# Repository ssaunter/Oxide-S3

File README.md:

# Oxide-S3
Oxide-S3 is a retro Spotify interface featuring a large TFT screen, a small OLED screen, 6 tactile switches, and 2 rotary encoders, all running on an ESP32-WROOM-1.

The device uses three seperate PCBs, one for the front, one for the top, and one for the side. The front PCB includes the displays, LiPo battery management, the MCU, and USB-C for charging. The top PCB includes the 6 Cherry MX Blue switches, and one of the rotary encoders. The side PCB simply includes the final rotary encoder. The small PCBs are connected to the front PCB using JST-XH cables.

# The PCBs

Front PCB:

Top PCB:

Side PCB:

Schematic:

# Assembly

The assembly is performed in several steps. First, 8 M3x5x5 threaded inserts are installed to the standoffs in the 3D printed front case. Then, the three PCBs are secured using M3x6 bolts.

 After the PCBs are installed, the battery holder module is press-fit into the front case, and the LiPo battery (red) is slid into place.

Then, the speaker and back case are press-fit into place. There is a 0.2mm tolerance built into the CAD model. 

Finally, the side and top knob are  press-fit onto the rotary encoders. This concludes the assembly.

# Software

Taking inspiration from [Donatnan Jong](https://github.com/Dongathan-Jong), I plan to utilize Spotify's built-in [developer interface](https://developer.spotify.com/) and Adafruit display libraries to program the screens in the Arduino IDE. Since Wifi is easily handled by the ESP32 and the switches handled by Spotify's interface, the main focus would be on managing the displays. Given my short project turnaround time, I will update this repo once parts arrive.

The TFT screen will be controlled through SPI, and the OLED through I2C. To add images, I'll use a bitmap tool to add features. Below are the major functions of the two displays:

Required Libraries:
---
```
#include <Arduino.h>
#include <ArduinoJson.h>
#include <Adafruit_GFX.h>
#include <Adafruit_ST7735.h>
#include <WiFi.h>
#include <SpotifyEsp32.h>
#include <SPI.h>
```

|3.5" TFT|
| :---: |
|Spotify symbol|
|Song timestamp|
|Audio wave animation|
|Key switch/encoder map|
|Album navigation|
|Spotify username|

|0.91" OLED|
| :---: |
|Battery charge status|
|Clock|
|Volume/Mute symbol|
|Wifi status|

Like I mentioned, this project is super last minute (started less than a day ago). I'll write the code and update this repo once I recieve the parts, and show off what the Oxide-S3 can do. Here's an example of how simple the code can be, written by [Donatnan Jong](https://github.com/Dongathan-Jong/SpotifyDisplay/?tab=readme-ov-file):

# BOM

| Part | Quantity | Price Per | Link | 
| :--- | :---: | :---: | :--- |
| **0.91" OLED** | 1 | $1.95 | [AliExpress](https://www.aliexpress.us/item/3256806449757543.html) |
| **3.5" TFT** | 1 | $10.45 | [AliExpress](https://www.aliexpress.us/item/3256801812264108.html) |  
| **ESP32-S3-WROOM-1-N8R8** | 1 | $6.13 | [DigiKey](https://www.digikey.com/short/wq4p3rwv) |
| **LDO** | 1 | $0.22 | [DigiKey](https://www.digikey.com/short/b2m9hq2c) |
| **Battery Charger** | 1 | $0.47 | [DigiKey](https://www.digikey.com/short/dz9hbfw5) |
| **USB-C Recepticle** | 1 | $0.78 | [DigiKey](https://www.digikey.com/short/rnhfh9zp) |
| **Rotary Encoder** | 2 | $1.72 | [DigiKey](https://www.digikey.com/short/1mq4zdpt) |
| **Boot Button** | 1 | $0.56 |[DigiKey](https://www.digikey.com/short/q5bt28qt) |
| **Slide Switch** | 1 | $0.65 | [DigiKey](https://www.digikey.com/short/41mc094h) |
| **1x2 JST-PH** | 1 | $0.11 | [DigiKey](https://www.digikey.com/short/41b2w40z) |
| **1x10 JST-XH** | 2 | $0.32 |[DigiKey](https://www.digikey.com/short/5571c5z5) |
| **1x4 JST-XH** | 2 | $0.14 | [DigiKey](https://www.digikey.com/short/h5trn14w) |
| **1.2k R 0603** | 1 | $0.10 |[DigiKey](https://www.digikey.com/short/hnr0jfrp) |
| **5.1k R 0603** | 2 | $0.10 |[DigiKey](https://www.digikey.com/short/mmd3843z) |
| **10k R 0603** | 1 | $0.10 | [DigiKey](https://www.digikey.com/short/p59dnbn3) |
| **0.1uF C 0603** | 2 | $0.12 |[DigiKey](https://www.digikey.com.au/short/w83wjqbv) |
| **10uF C 0603** | 2 | $0.35 |[DigiKey](https://www.digikey.com/short/5dtppp4z) |
| **DSA Keycaps 10pcs** | 1 | (have) |[DigiKey](https://www.digikey.com/short/p4j0ztf5) |
| **Cherry MX Blue 10pcs** | 1 | $4.00 |[MechanicalKeyboards](https://mechanicalkeyboards.com/products/cherry-mx-blue-60g-clicky) |
| **1x10 JST-XH Jumper** | 1 | $3.40 |[AliExpress](https://www.aliexpress.us/item/3256807069159656.html) |
| **1x4 JST-XH Jumper** | 1 | $2.36 |[AliExpress](https://www.aliexpress.us/item/3256807069159656.html) |
| **1S 1500mAh LiPo** | 1 | (have) |[SparkFun](https://www.sparkfun.com/lithium-ion-battery-1500mah-iec62133-certified.html#content-documentation) |
| **MicroSD** | 1 | (have) | |
| **M3x6 Bolt** | 8 | (have) | |
| **M3x5x5 Threaded Insert** | 8 | (have) | |

Totals
---
| Service  | Price | 
| :--- | :--- |
| **JLCPCB Order** | $48.49 | |
| **DigiKey Order** | $32.36 | 
| **AliExpress Order** |  $19.44 | 
| **MechanicalKeyboards Order** |  $9.52 | 

This total comes out to $109.81 which is slightly over my limit. I'll downgrade to some generic Cherry MX Red switches, and some old DSA switches, both which I alreday have bringing the total to **$94.34**.

Orders:

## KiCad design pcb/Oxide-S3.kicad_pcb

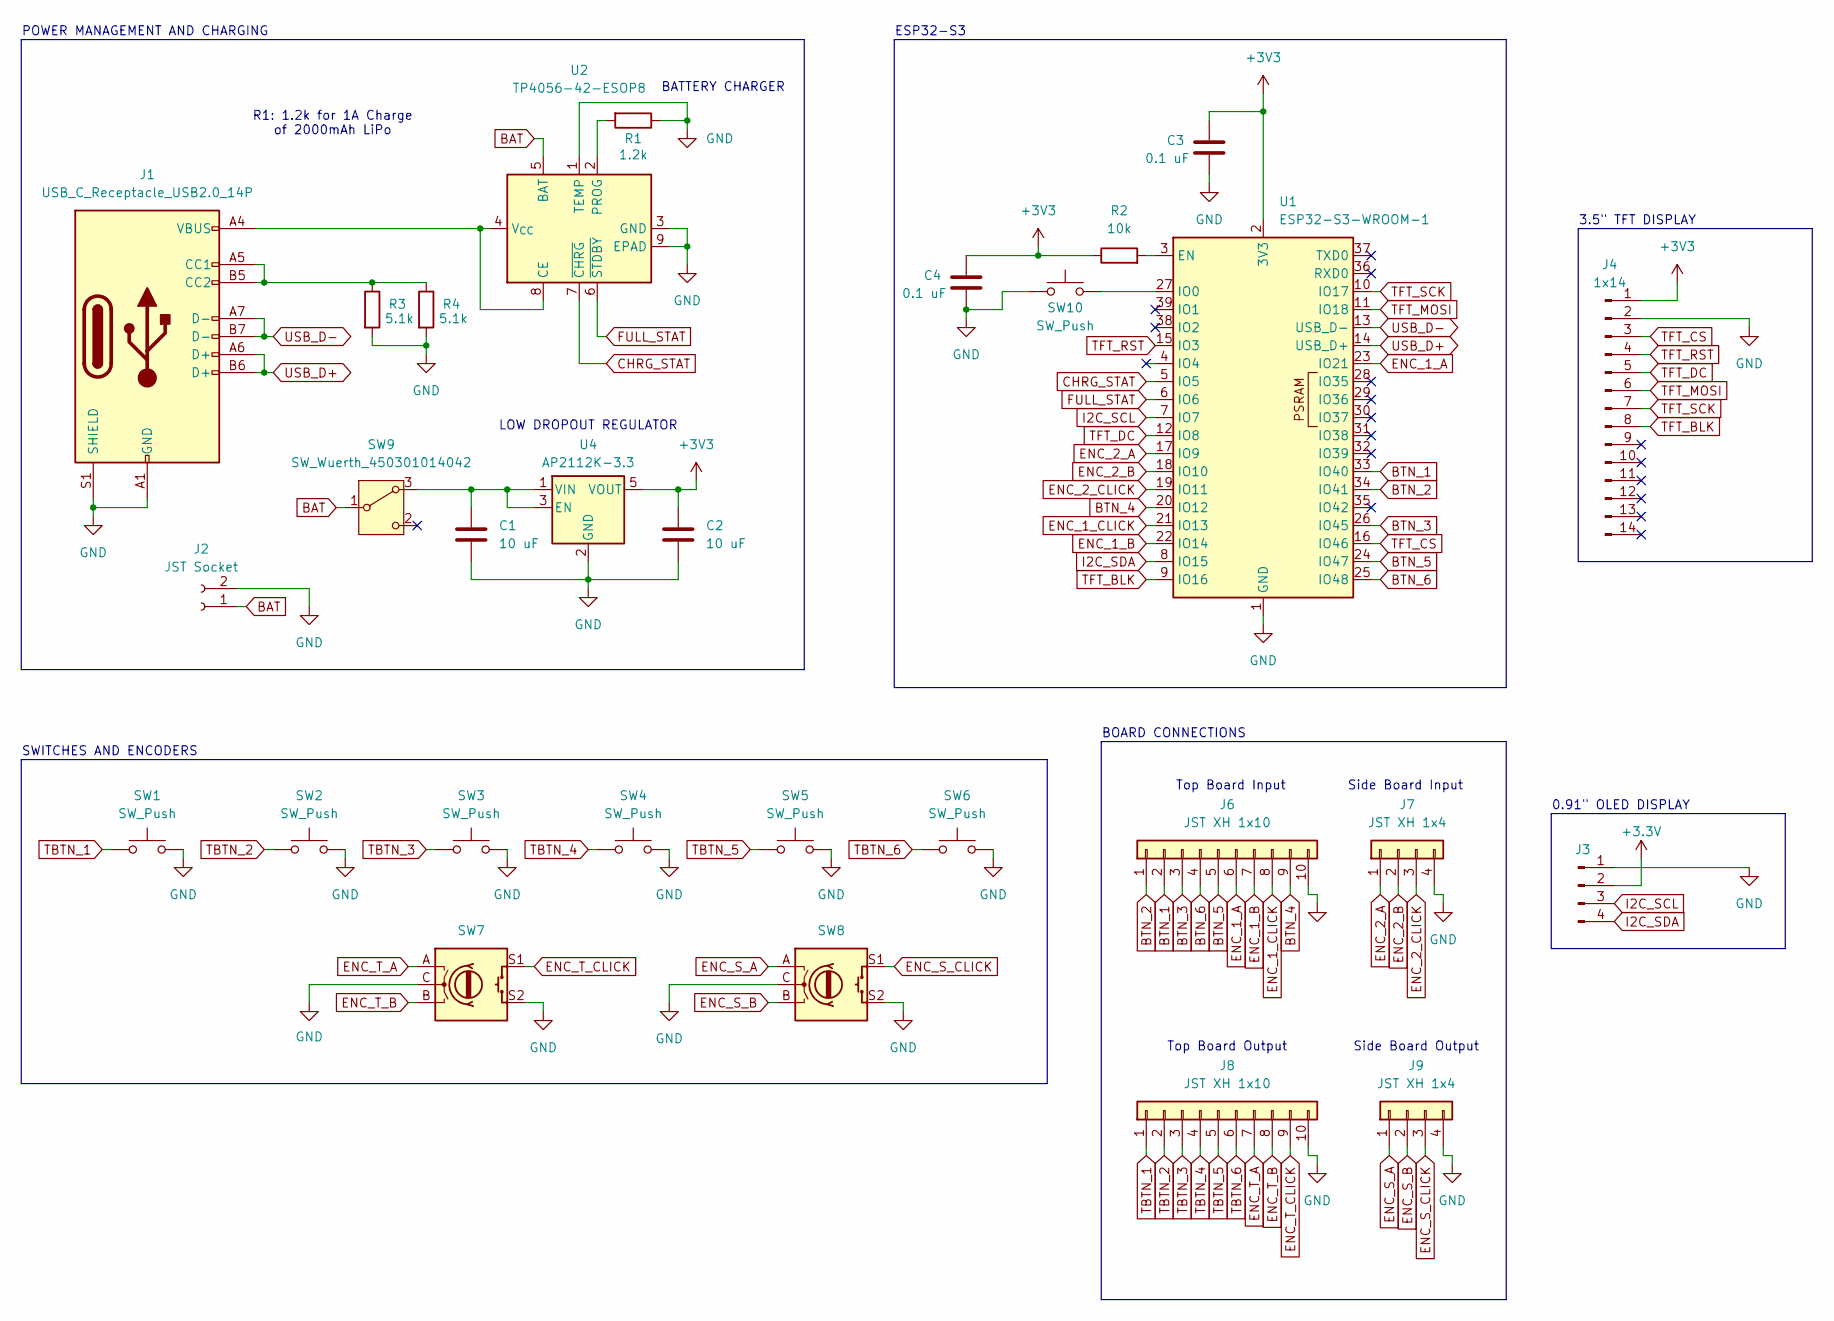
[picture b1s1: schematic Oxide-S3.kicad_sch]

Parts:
C1, C2: 10 uF; C_0603_1608Metric
C3, C4: 0.1 uF; C_0603_1608Metric
J1: USB_C_Receptacle_USB2.0_14P; USB_C_Receptacle_HRO_TYPE-C-31-M-12
J2: JST Socket; JST_PH_S2B-PH-K_1x02_P2.00mm_Horizontal
J3: OLED_DISPLAY; SSD1306-0.91-OLED-4pin-128x32
J4: 1x14; 3.5_TFT_Screen
J6, J8: JST XH 1x10; JST_XH_B10B-XH-A_1x10_P2.50mm_Vertical
J7, J9: JST XH 1x4; JST_XH_B4B-XH-A_1x04_P2.50mm_Vertical
R1: 1.2k; R_0603_1608Metric
R2: 10k; R_0603_1608Metric
R3, R4: 5.1k; R_0603_1608Metric
SW1, SW2, SW3, SW4, SW5, SW6: SW_Push; SW_Cherry_MX_1.00u_PCB
SW7, SW8: RotaryEncoder_Switch; RotaryEncoder_Alps_EC11E-Switch_Vertical_H20mm
SW9: SW_Wuerth_450301014042; SW_Slide_SPDT_Angled_CK_OS102011MA1Q
SW10: SW_Push; SW_SPST_Omron_B3FS-100xP
U1: ESP32-S3-WROOM-1
U2: TP4056-42-ESOP8; SOIC-8-1EP_3.9x4.9mm_P1.27mm_EP2.41x3.3mm_ThermalVias
U4: AP2112K-3.3; SOT-23-5

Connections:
+3.3V: J3.2
+3V3: C2.1, C3.1, C4.1, J4.1, R2.1, U1.2 (3V3), U4.5 (VOUT)
BAT: J2.1, SW9.1 (B), U2.5 (BAT)
BTN_1: J6.2, U1.33 (IO40)
BTN_2: J6.1, U1.34 (IO41)
BTN_3: J6.3, U1.26 (IO45)
BTN_4: J6.9, U1.20 (IO12)
BTN_5: J6.5, U1.24 (IO47)
BTN_6: J6.4, U1.25 (IO48)
CHRG_STAT: U1.5 (IO5), U2.7 (~CHRG)
ENC_1_A: J6.6, U1.23 (IO21)
ENC_1_B: J6.7, U1.22 (IO14)
ENC_1_CLICK: J6.8, U1.21 (IO13)
ENC_2_A: J7.1, U1.17 (IO9)
ENC_2_B: J7.2, U1.18 (IO10)
ENC_2_CLICK: J7.3, U1.19 (IO11)
ENC_S_A: J9.1, SW8.A
ENC_S_B: J9.2, SW8.B
ENC_S_CLICK: J9.3, SW8.S1
ENC_T_A: J8.7, SW7.A
ENC_T_B: J8.8, SW7.B
ENC_T_CLICK: J8.9, SW7.S1
FULL_STAT: U1.6 (IO6), U2.6 (~STDBY)
GND: C1.2, C2.2, C3.2, C4.2, J1.A1 (GND), J1.A12 (GND), J1.B1 (GND), J1.B12 (GND), J1.S1 (SHIELD), J2.2, J3.1, J4.2, J6.10, J7.4, J8.10, J9.4, R1.1, R3.2, R4.2, SW1.2, SW2.2, SW3.2, SW4.2, SW5.2, SW6.2, SW7.C, SW7.S2, SW8.C, SW8.S2, SW10.1, U1.1 (GND), U1.40 (GND), U1.41 (GND), U2.1 (TEMP), U2.3 (GND), U2.9 (EPAD), U4.2 (GND)
I2C_SCL: J3.3, U1.7 (IO7)
I2C_SDA: J3.4, U1.8 (IO15)
unnamed: J1.A5 (CC1), J1.B5 (CC2), R3.1, R4.1
unnamed: C1.1, SW9.3 (A), U4.1 (VIN), U4.3 (EN)
unnamed: R2.2, U1.3 (EN)
unnamed: SW10.2, U1.27 (IO0)
unnamed: J1.A4 (VBUS), J1.A9 (VBUS), J1.B4 (VBUS), J1.B9 (VBUS), U2.4 (V_{CC}), U2.8 (CE)
unnamed: R1.2, U2.2 (PROG)
TBTN_1: J8.1, SW1.1
TBTN_2: J8.2, SW2.1
TBTN_3: J8.3, SW3.1
TBTN_4: J8.4, SW4.1
TBTN_5: J8.5, SW5.1
TBTN_6: J8.6, SW6.1
TFT_BLK: J4.8, U1.9 (IO16)
TFT_CS: J4.3, U1.16 (IO46)
TFT_DC: J4.5, U1.12 (IO8)
TFT_MOSI: J4.6, U1.11 (IO18)
TFT_RST: J4.4, U1.15 (IO3)
TFT_SCK: J4.7, U1.10 (IO17)
USB_D+: J1.A6 (D+), J1.B6 (D+), U1.14 (USB_D+)
USB_D-: J1.A7 (D-), J1.B7 (D-), U1.13 (USB_D-)

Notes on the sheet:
ESP32-S3
Side Board Output
3.5" TFT DISPLAY
0.91" OLED DISPLAY
BATTERY CHARGER
POWER MANAGEMENT AND CHARGING
Top Board Input
Side Board Input
Top Board Output
BOARD CONNECTIONS
R1: 1.2k for 1A Charge of 2000mAh LiPo
LOW DROPOUT REGULATOR
SWITCHES AND ENCODERS

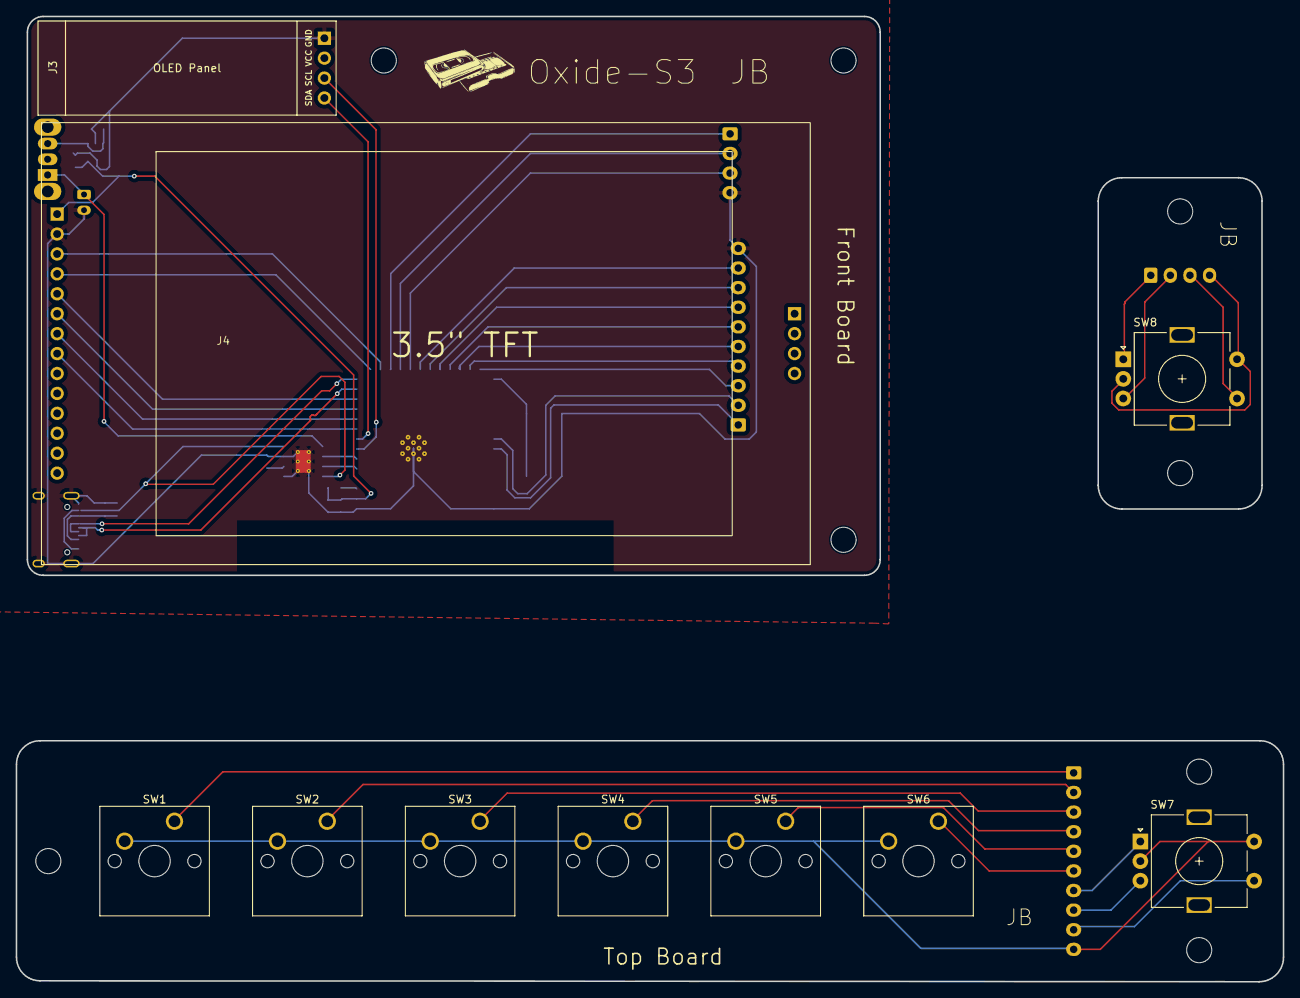
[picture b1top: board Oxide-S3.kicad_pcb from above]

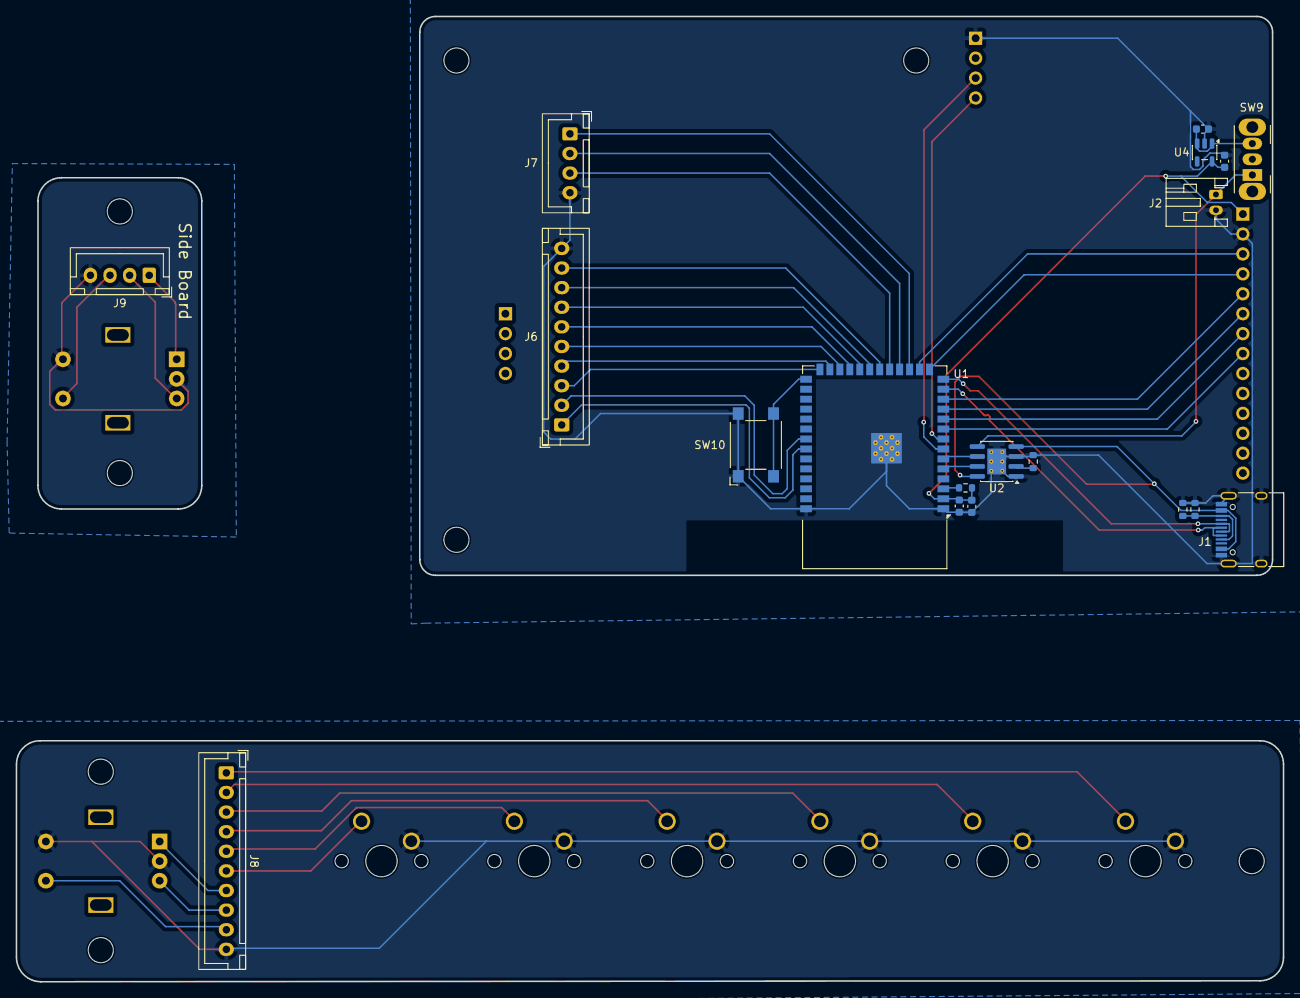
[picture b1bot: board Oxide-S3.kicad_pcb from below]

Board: 2 copper layers, 161.5 x 123.0 mm, 29 parts (19 on the bottom side), 45 nets.

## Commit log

2026-03-31 main commit
    added everything
2026-03-31 added references
2026-03-31 updated mds
2026-03-31 updated bom
2026-03-31 fixed csv
2026-03-31 updated csv
2026-03-31 added full cad and updated readme
2026-04-27 added f3z file
